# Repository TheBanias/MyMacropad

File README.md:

# MyMacropad

A 6–key macropad based on a **Seeed Studio XIAO RP2040**, designed for quick shortcuts on Windows 10: open a new browser tab, take screenshots, and launch Steam and Discord.

---

## Overall hackpad screenshot

Screenshot of the complete hackpad (assembled):

---

## Schematic screenshot

This is the electrical schematic used to wire the XIAO RP2040, switches and connectors:

---

## PCB screenshot

Top view of the custom PCB designed in KiCad:

---

## Case and fit

The macropad case is split into two main parts: a base and a top cover.  
They are provided as STEP files so they can be edited or re‑exported as STLs for 3D printing.

- `CAD/macropad.step` – full assembly of the case.  
- `CAD/Macropad_top.step` – separate top piece.

The image below shows the overall case geometry and how the plate and switches fit inside:

---

## Bill of Materials (BOM)

| Qty | Part                              | Notes                                      |
|-----|-----------------------------------|--------------------------------------------|
| 1   | Seeed Studio **XIAO RP2040**      | Main microcontroller board                 |
| 6   | Mechanical key switch (MX style)  | Any MX‑compatible switch                   |
| 6   | Keycaps                           | MX‑compatible                              |
| 1   | Custom PCB (MACROPAD.kicad_pcb)   | From `PCB/` folder                         |
| 1   | 3D printed case (base + top)      | From `CAD/macropad.step` / `Macropad_top.step` |
| 4   | M3 screws (and inserts, optional) | For mounting the case                      |
| —   | Wire / headers                    | If hand‑wiring or socketing the XIAO       |

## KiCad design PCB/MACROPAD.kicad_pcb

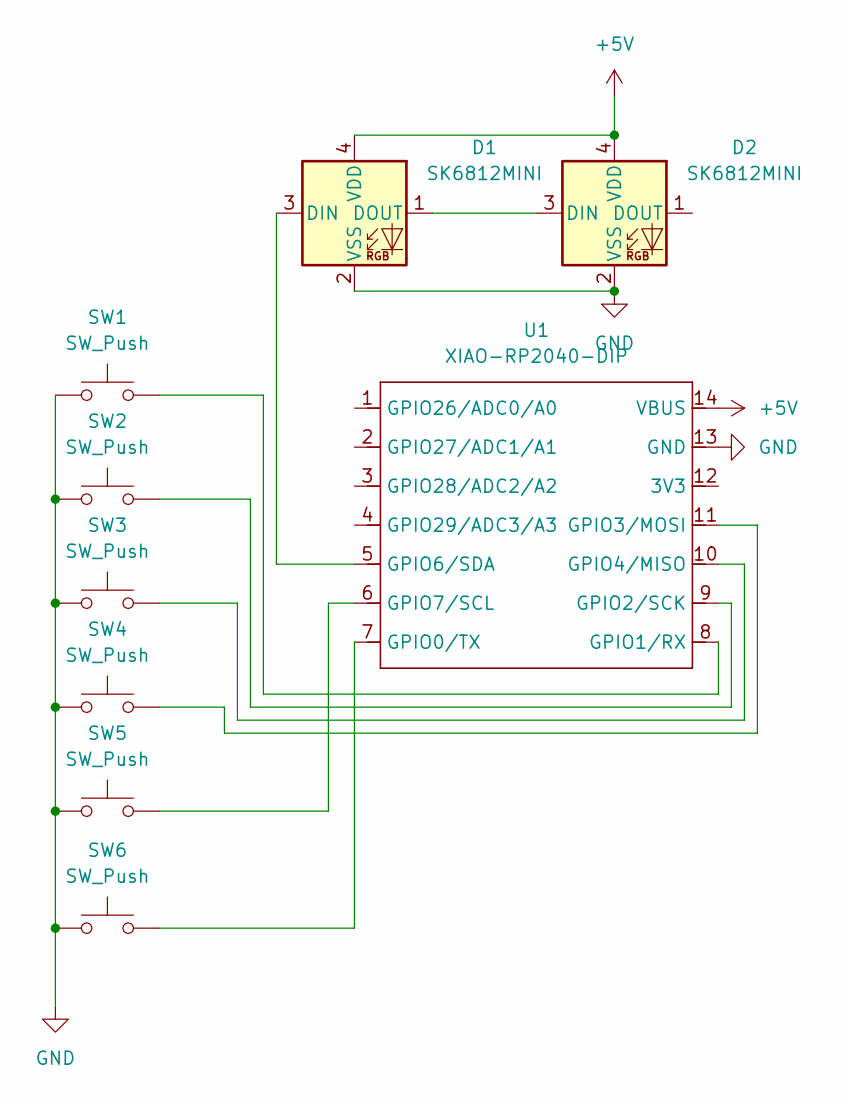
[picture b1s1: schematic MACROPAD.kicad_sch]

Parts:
D1, D2: SK6812MINI; LED_SK6812MINI_PLCC4_3.5x3.5mm_P1.75mm
SW1, SW2, SW3, SW4, SW5, SW6: SW_Push; SW_Cherry_MX_1.00u_PCB
U1: XIAO-RP2040-DIP; XIAO-RP2040-SMD

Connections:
+5V: D1.4 (VDD), D2.4 (VDD), U1.14 (VBUS)
GND: D1.2 (VSS), D2.2 (VSS), SW1.1, SW2.1, SW3.1, SW4.1, SW5.1, SW6.1, U1.13 (GND)
unnamed: D1.3 (DIN), U1.5 (GPIO6/SDA)
unnamed: D1.1 (DOUT), D2.3 (DIN)
unnamed: SW6.2, U1.7 (GPIO0/TX)
unnamed: SW1.2, U1.8 (GPIO1/RX)
unnamed: SW2.2, U1.9 (GPIO2/SCK)
unnamed: SW4.2, U1.11 (GPIO3/MOSI)
unnamed: SW3.2, U1.10 (GPIO4/MISO)
unnamed: SW5.2, U1.6 (GPIO7/SCL)

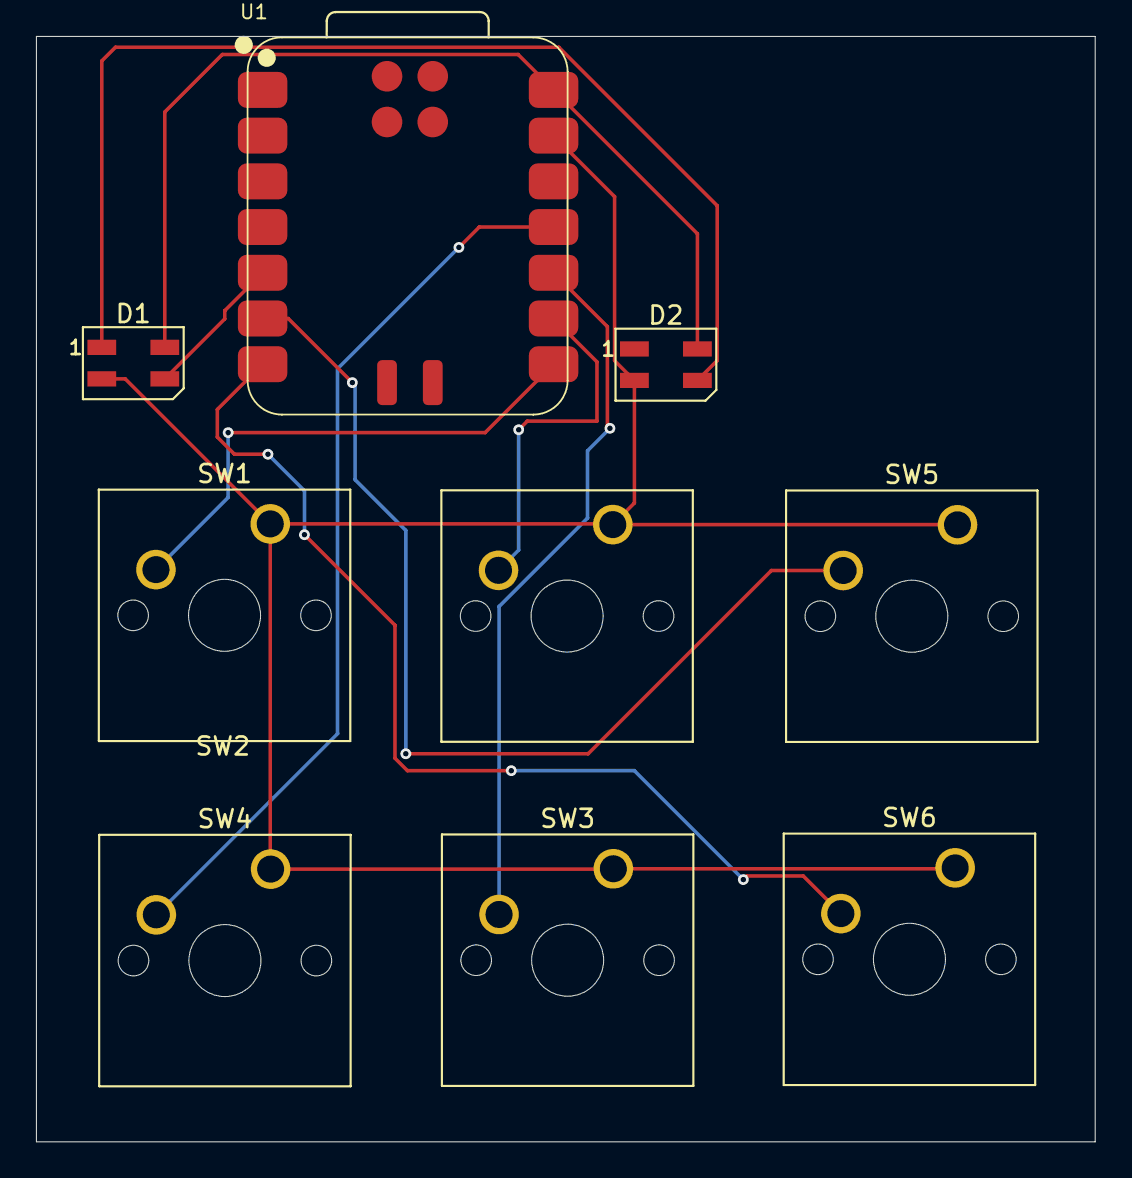
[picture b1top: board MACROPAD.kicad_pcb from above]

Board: 2 copper layers, 58.8 x 61.4 mm, 9 parts (0 on the bottom side), 10 nets.

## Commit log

2025-12-23 Agregado todos los archivos
2025-12-23 readme
2025-12-23 Imagenes corregidas
2025-12-23 Readme arrglado
2025-12-24 rehecho
2025-12-24 readme actualizado
2025-12-24 readme definitivo
2025-12-24 6 keys
